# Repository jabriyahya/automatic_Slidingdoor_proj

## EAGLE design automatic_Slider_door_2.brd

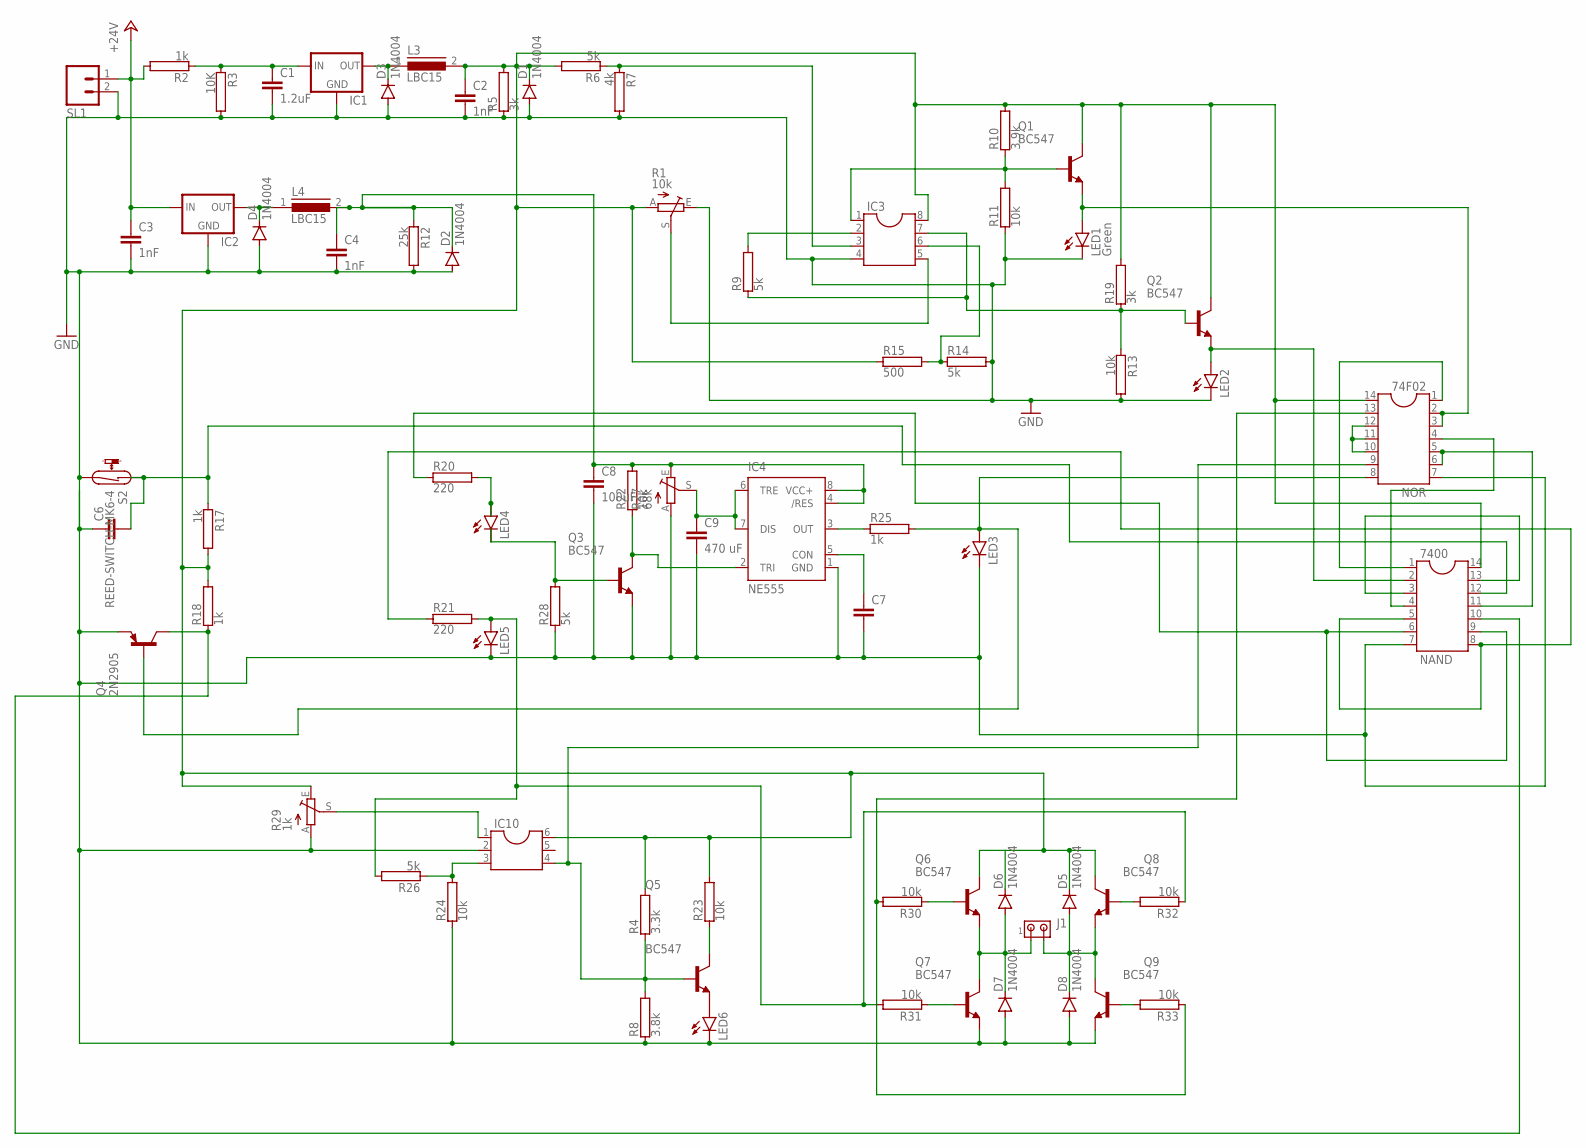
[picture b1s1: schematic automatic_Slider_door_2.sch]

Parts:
74F02: NOR; DIL14
7400: NAND; DIL14
C1: 1.2uF; C2.5-3
C2, C3, C4: 1nF; C2.5-3
C6, C7: C2,5-3; C2.5-3
C8: 100uF; C2.5-3
C9: 470 uF; C2.5-3
D1, D2, D3, D4, D5, D6, D7, D8: 1N4004; DO41-10
IC1, IC2: 78LXX
IC3: DIL8S; SOCKET-08
IC4: NE555; DIL-08
IC10: DIL6S; SOCKET-06
J1: MTA02-156; 1X2MTA
L3, L4: LBC15
LED1: Green; Q62902-B152
LED2, LED3, LED4, LED5, LED6: LEDB152; Q62902-B152
Q1, Q2, Q3, Q5, Q6, Q7, Q8, Q9: BC547; TO92
Q4: 2N2905; TO5
R1: 10k; S75P
R2, R17, R18, R25: 1k; CA0001
R3: 10K; CA0001
R4: 3.3k; CA0001
R5, R19: 3k; CA0001
R6, R9, R14, R26, R28: 5k; CA0001
R7: 4k; CA0001
R8: 3.8k; CA0001
R10: 3.9k; CA0001
R11, R13, R22, R23, R24, R30, R31, R32, R33: 10k; CA0001
R12: 25k; CA0001
R15: 500; CA0001
R20, R21: 220; CA0001
R27: 68k; S75P
R29: 1k; S75P
S2: REED-SWITCH-MK6-4; MK6-4
SL1: MA02; 02PA

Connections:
+24V: C3.1, IC2.IN, R2.2, SL1.1
GND: 74F02.7, 7400.7, C1.2, C2.2, C3.2, C4.2, C6.1, C7.2, C8.2, C9.2, D1.A, D2.A, D3.A, D4.A, D7.A, D8.A, IC1.GND, IC2.GND, IC3.4, IC4.1 (GND), IC10.2, LED1.K (C), LED2.K (C), LED3.K (C), LED5.K (C), LED6.K (C), Q3.1 (E), Q4.1 (E), Q7.1 (E), Q9.1 (E), R1.E, R3.2, R5.1, R7.2, R8.1, R11.1, R12.2, R13.2, R14.2, R24.1, R27.A, R28.1, R29.A, S2.2, SL1.2
unnamed: IC3.5, R1.S
unnamed: C1.1, IC1.IN, R2.1, R3.1
unnamed: 7400.2, LED2.A, Q2.1 (E)
unnamed: D3.C, IC1.OUT, L3.1
unnamed: 7400.5, 7400.8, R21.1
unnamed: IC3.2, R9.2
unnamed: IC3.6, R14.1, R15.2
unnamed: IC3.7, Q2.2 (B), R9.1, R13.1, R19.1
unnamed: IC3.3, R6.1, R7.1
unnamed: IC3.1, Q1.2 (B), R10.1, R11.2
unnamed: 7400.3, 7400.13
unnamed: 74F02.9, IC10.4, Q5.2 (B), R4.1, R8.2
unnamed: IC4.3 (OUT), R25.1
unnamed: Q9.2 (B), R33.2
unnamed: 7400.12, C6.2, R17.1, S2.1
unnamed: 74F02.2, 74F02.3, LED1.A, Q1.1 (E)
unnamed: 74F02.5, 74F02.6, 7400.11
unnamed: IC10.3, R24.2, R26.1
unnamed: LED4.A, R20.2
unnamed: 7400.10, Q4.3 (C), R18.1
unnamed: LED6.A, Q5.1 (E)
unnamed: C4.1, C8.1, D2.C, IC4.4 (/RES), IC4.8 (VCC+), L4.2, R12.1, R22.2, R27.E
unnamed: LED5.A, R21.2, R26.2, R31.2, R32.1
unnamed: C9.1, IC4.6 (TRE), IC4.7 (DIS), R27.S
unnamed: IC4.2 (TRI), Q3.3 (C), R22.1
unnamed: 74F02.4, 7400.4
unnamed: IC10.1, R29.S
unnamed: 74F02.8, LED3.A, Q4.2 (B), R25.2
unnamed: C7.1, IC4.5 (CON)
unnamed: LED4.K (C), Q3.2 (B), R28.2
unnamed: 74F02.10, 74F02.11, 74F02.12
unnamed: 7400.6, 7400.9, R20.1
unnamed: 74F02.1, 7400.1
unnamed: D4.C, IC2.OUT, L4.1
unnamed: 74F02.13, R30.2, R33.1
unnamed: D6.A, D7.C, J1.1, Q6.1 (E), Q7.3 (C)
unnamed: Q8.2 (B), R32.2
unnamed: 74F02.14, 7400.14, C2.1, D1.C, D5.C, D6.C, IC3.8, IC10.6, L3.2, Q1.3 (C), Q2.3 (C), Q6.3 (C), Q8.3 (C), R1.A, R4.2, R5.2, R6.2, R10.2, R15.1, R17.2, R18.2, R19.2, R23.2, R29.E
unnamed: Q5.3 (C), R23.1
unnamed: D5.A, D8.C, J1.2, Q8.1 (E), Q9.3 (C)
unnamed: Q7.2 (B), R31.1
unnamed: Q6.2 (B), R30.1

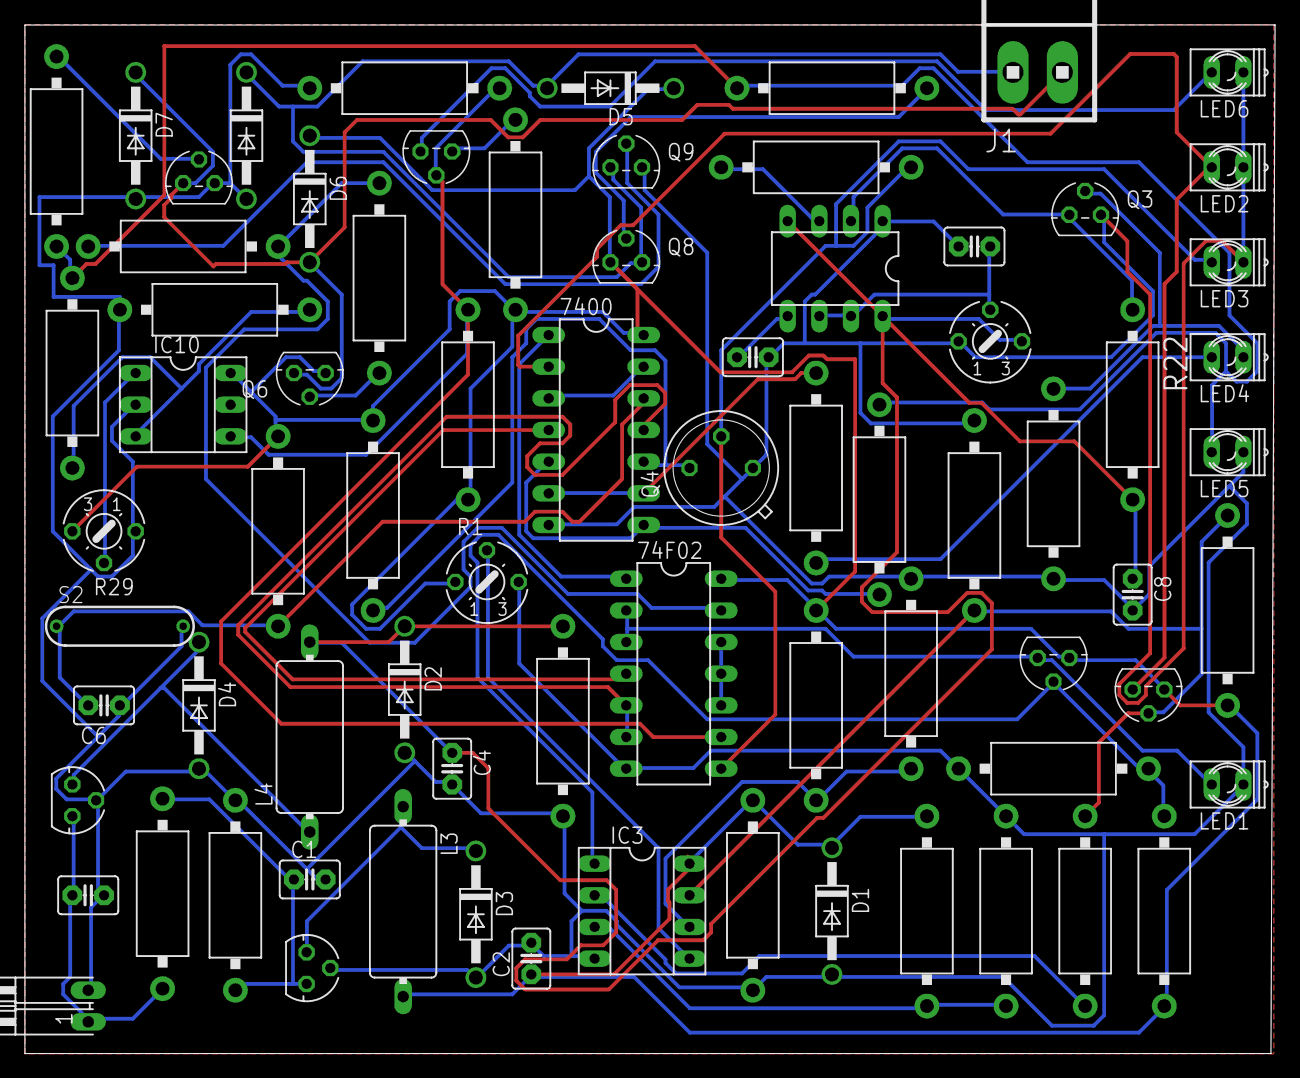
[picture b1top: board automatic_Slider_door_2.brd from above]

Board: 2 copper layers, 100.3 x 82.5 mm, 75 parts (0 on the bottom side), 44 nets.
